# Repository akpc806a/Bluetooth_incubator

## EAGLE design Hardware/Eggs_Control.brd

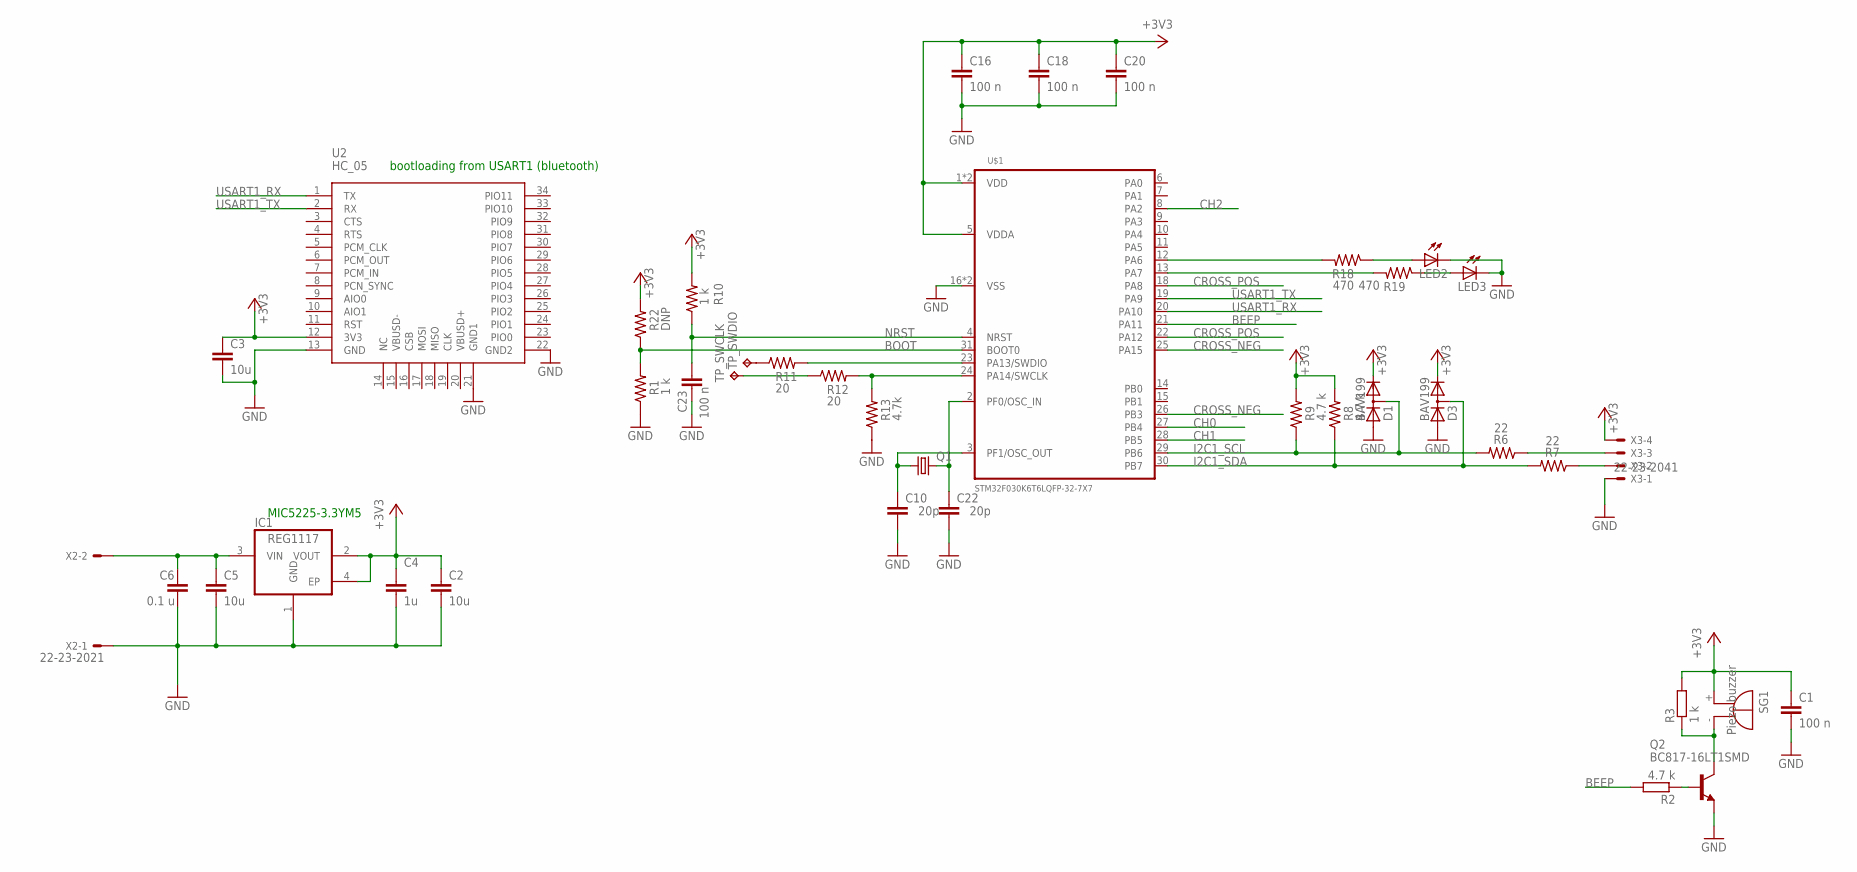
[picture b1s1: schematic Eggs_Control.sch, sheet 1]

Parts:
C1, C16, C18, C20, C23: 100 n; C0603
C2, C3, C5: 10u; C0805
C4: 1u; C0603
C6: 0.1 u; C0603
C10, C22: 20p; C0603
D1, D3: BAV199; SOT23
IC1: REG1117; SOT223
LED2, LED3: LED_ESML0603; LED_SML0603
Q1: CRYSTALSM49; SM49
Q2: BC817-16LT1SMD; SOT23-BEC
R1, R3, R10: 1 k; R0603
R2, R8, R9: 4.7 k; R0603
R6, R7: 22; R0603
R11, R12: 20; R0603
R13: 4.7k; R0603
R18, R19: 470; R0603
R22: DNP; R0603
SG1: Piezo buzzer; F/HMB
TP_SWCLK: TPTP10SQ; TP10SQ
TP_SWDIO: TPTP10SQ; TP10SQ
U2: HC_05; BLUETOOTH_SMD
U$1: STM32F030K6T6LQFP-32-7X7; LQFP32-7X7
X2: 22-23-2021
X3: 22-23-2041

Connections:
+3V3: C1.1, C2.1, C3.1, C4.1, C16.1, C18.1, C20.1, D1.2 (C), D3.2 (C), IC1.2 (VOUT), IC1.4 (EP), R3.2, R8.2, R9.2, R10.2, R22.2, SG1.+, U2.12 (3V3), U$1.1 (VDD), U$1.5 (VDDA), U$1.17 (VDD), X3.4; also elsewhere on the board
BEEP: R2.2, U$1.21 (PA11)
BOOT: R1.2, R22.1, U$1.31 (BOOT0)
CH0: U$1.27 (PB4); also elsewhere on the board
CH1: U$1.28 (PB5); also elsewhere on the board
CH2: U$1.8 (PA2); also elsewhere on the board
CROSS_NEG: U$1.25 (PA15), U$1.26 (PB3); also elsewhere on the board
CROSS_POS: U$1.18 (PA8), U$1.22 (PA12); also elsewhere on the board
GND: C1.2, C2.2, C3.2, C4.2, C5.2, C6.2, C10.2, C16.2, C18.2, C20.2, C22.2, C23.2, D1.1 (A), D3.1 (A), IC1.1 (GND), LED2.C, LED3.C, Q2.E, R1.1, R13.1, U2.13 (GND), U2.21 (GND1), U2.22 (GND2), U$1.16 (VSS), U$1.32 (VSS), X2.1, X3.1; also elsewhere on the board
I2C1_SCL: D1.3 (AC), R6.2, R9.1, U$1.29 (PB6)
I2C1_SDA: D3.3 (AC), R7.2, R8.1, U$1.30 (PB7)
unnamed: Q2.B, R2.1
unnamed: Q2.C, R3.1, SG1.-
unnamed: R18.2, U$1.12 (PA6)
unnamed: R19.2, U$1.13 (PA7)
unnamed: R7.1, X3.2
unnamed: R6.1, X3.3
unnamed: LED2.A, R18.1
unnamed: LED3.A, R19.1
unnamed: R11.2, U$1.23 (PA13/SWDIO)
unnamed: R12.2, R13.2, U$1.24 (PA14/SWCLK)
unnamed: R11.1, TP_SWDIO.TP
unnamed: R12.1, TP_SWCLK.TP
unnamed: C5.1, C6.1, IC1.3 (VIN), X2.2
unnamed: C22.1, Q1.2, U$1.2 (PF0/OSC_IN)
unnamed: C10.1, Q1.1, U$1.3 (PF1/OSC_OUT)
NRST: C23.1, R10.1, U$1.4 (NRST)
USART1_RX: U2.1 (TX), U$1.20 (PA10)
USART1_TX: U2.2 (RX), U$1.19 (PA9)

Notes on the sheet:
MIC5225-3.3YM5
bootloading from USART1 (bluetooth)

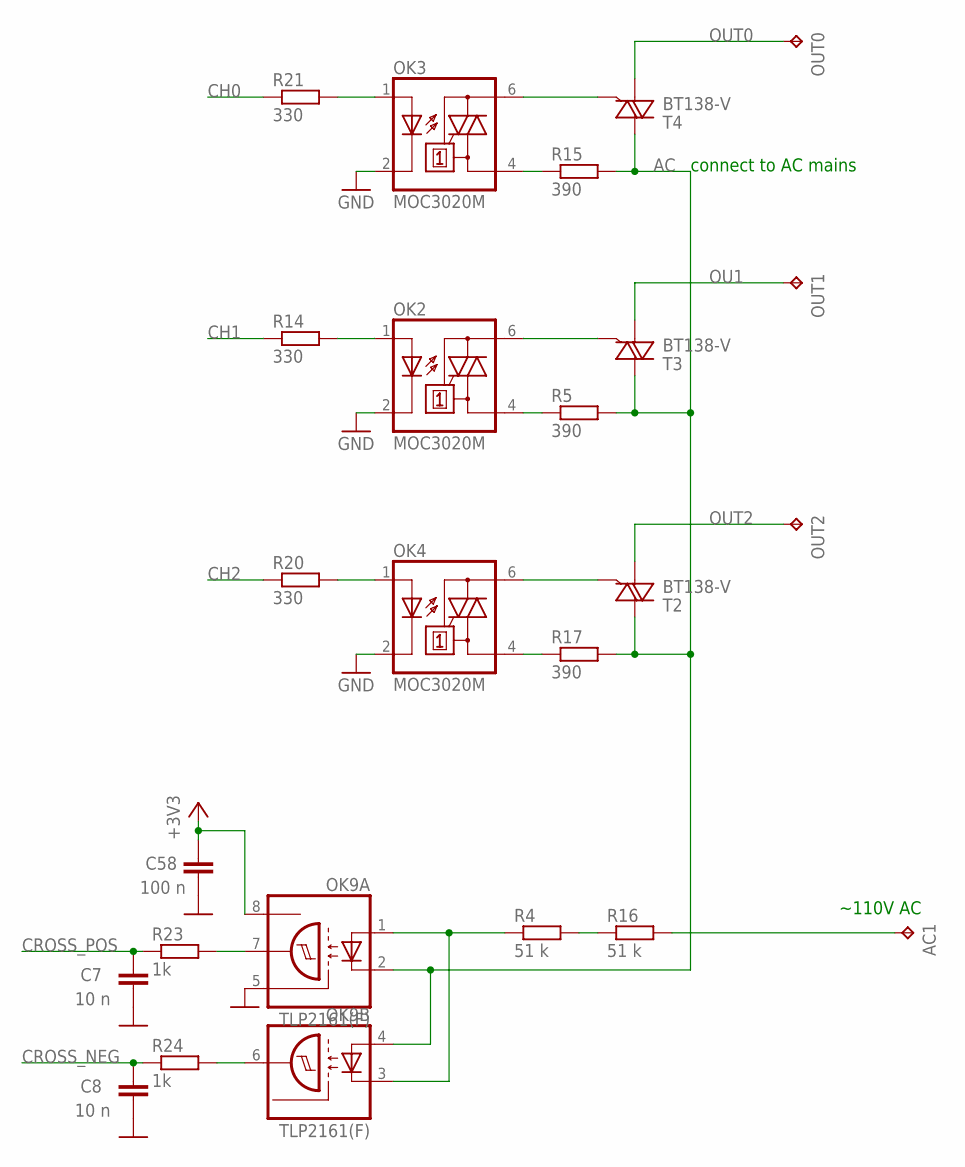
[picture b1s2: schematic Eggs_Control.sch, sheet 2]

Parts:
AC1: TPPAD1-17; P1-17
C7, C8: 10 n; C0603
C58: 100 n; C0603
OK2, OK3, OK4: MOC3020M; DIL06
OK9: TLP2161(F); SOIC08-FAIRCHILD
OUT0, OUT1, OUT2: TPPAD1-17; P1-17
R4, R16: 51 k; R1206
R5, R15, R17: 390; R0603
R14, R20, R21: 330; R0603
R23, R24: 1k; R0603
T2, T3, T4: BT138-V; TO220BV

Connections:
+3V3: C58.1, OK9.8 (VCC); also elsewhere on the board
AC: OK9.2 (C), OK9.4 (A), R5.2, R15.2, R17.2, T2.T2 (A2), T3.T2 (A2), T4.T2 (A2)
CH0: R21.1; also elsewhere on the board
CH1: R14.1; also elsewhere on the board
CH2: R20.1; also elsewhere on the board
CROSS_NEG: C8.1, R24.1; also elsewhere on the board
CROSS_POS: C7.1, R23.1; also elsewhere on the board
GND: C7.2, C8.2, C58.2, OK2.2 (C), OK3.2 (C), OK4.2 (C), OK9.5 (GND); also elsewhere on the board
unnamed: OK9.1 (A), OK9.3 (C), R4.1
unnamed: AC1.TP, R16.2
unnamed: OK9.7 (OUT), R23.2
unnamed: OK9.6 (OUT), R24.2
unnamed: OK2.1 (A), R14.2
unnamed: R4.2, R16.1
unnamed: OK4.1 (A), R20.2
unnamed: OK4.4 (A1), R17.1
unnamed: OK4.6 (A2), T2.G
unnamed: OK2.4 (A1), R5.1
unnamed: OK2.6 (A2), T3.G
unnamed: OK3.1 (A), R21.2
unnamed: OK3.4 (A1), R15.1
unnamed: OK3.6 (A2), T4.G
OU1: OUT1.TP, T3.T1 (A1)
OUT0: OUT0.TP, T4.T1 (A1)
OUT2: OUT2.TP, T2.T1 (A1)

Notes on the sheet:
~110V AC
connect to AC mains

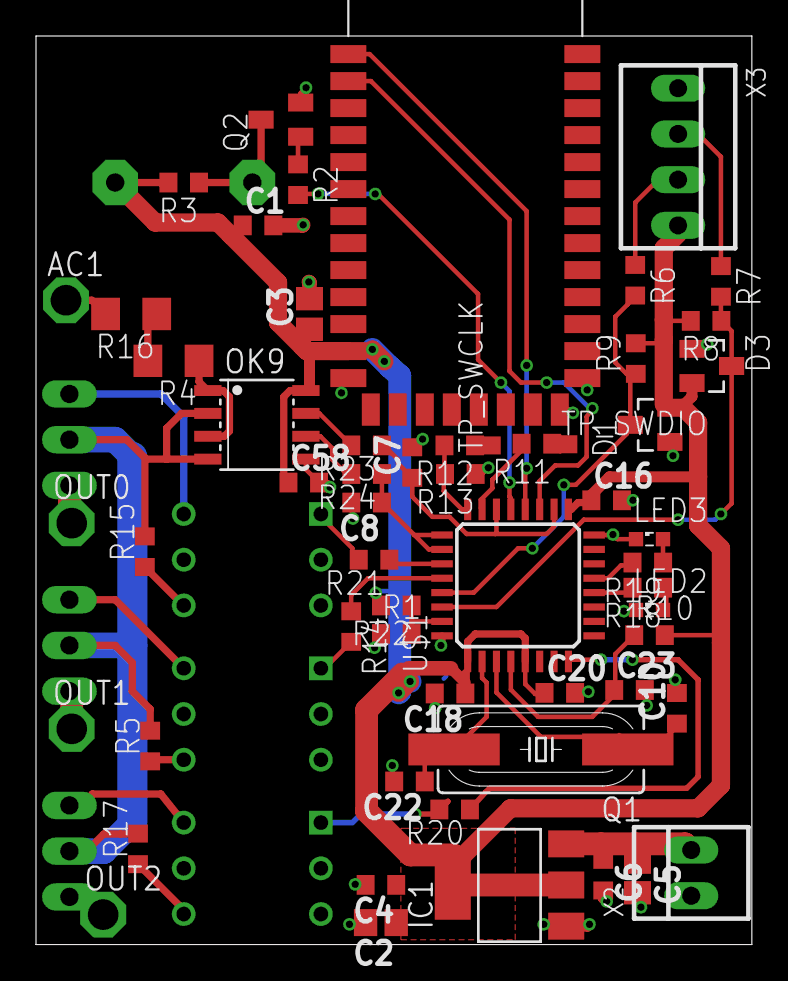
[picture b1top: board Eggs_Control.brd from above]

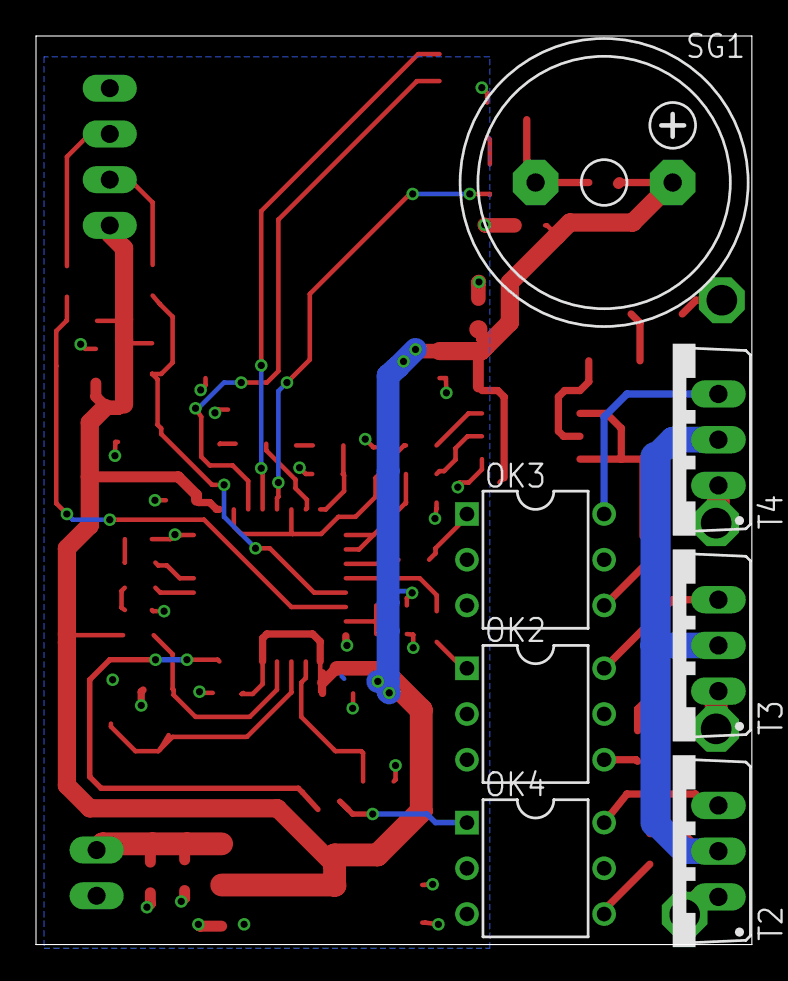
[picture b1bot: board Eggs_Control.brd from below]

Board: 2 copper layers, 39.8 x 50.5 mm, 64 parts (7 on the bottom side), 47 nets.

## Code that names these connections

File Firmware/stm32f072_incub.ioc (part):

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Mcu.Name=STM32F072R(8-B)Tx
Mcu.Package=LQFP64
Mcu.UserName=STM32F072RBTx
PA10.Mode=Asynchronous
PA10.Signal=USART1_RX
PA6.GPIOParameters=GPIO_Speed,GPIO_Label
PA6.GPIO_Label=LEDG
PA6.GPIO_Speed=GPIO_SPEED_HIGH
PA6.Signal=GPIO_Output
PA7.GPIOParameters=GPIO_Speed,GPIO_Label
PA7.GPIO_Label=LEDR
PA7.GPIO_Speed=GPIO_SPEED_HIGH
PA7.Signal=GPIO_Output
PA9.Mode=Asynchronous
PA9.Signal=USART1_TX
PB3.GPIOParameters=GPIO_Speed,GPIO_Label
PB3.GPIO_Label=CH1
PB3.GPIO_Speed=GPIO_SPEED_HIGH
PB3.Signal=GPIO_Output
PB6.Mode=I2C
PB6.Signal=I2C1_SCL
PB7.Mode=I2C
PB7.Signal=I2C1_SDA
PB9.GPIOParameters=GPIO_Speed,GPIO_Label
PB9.GPIO_Label=CH2
PB9.GPIO_Speed=GPIO_SPEED_HIGH
PB9.Signal=GPIO_Output
PC11.GPIOParameters=GPIO_Label
PC11.GPIO_Label=CROSS_POS
PC11.Signal=GPXTI11
PC12.GPIOParameters=GPIO_Label
PC12.GPIO_Label=CROSS_NEG
PC12.Signal=GPXTI12
PD2.GPIOParameters=GPIO_Speed,GPIO_Label
PD2.GPIO_Label=CH0
PD2.GPIO_Speed=GPIO_SPEED_HIGH
PD2.Signal=GPIO_Output
PF0-OSC_IN.Mode=HSE-External-Oscillator
PF0-OSC_IN.Signal=RCC_OSC_IN
PF1-OSC_OUT.Mode=HSE-External-Oscillator
PF1-OSC_OUT.Signal=RCC_OSC_OUT
RCC.SYSCLKFreq_VALUE=48000000
RCC.SYSCLKSource=RCC_SYSCLKSOURCE_PLLCLK
board=stm32f072_incub

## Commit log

2016-10-24 initial commit
    - hardware tested
    - firmware tested with PC computer software (including Modbus interface,
    temperature regulator, humidity control, timer)
2017-01-03 gitignore updated
2017-01-03 LEDs corrected
2017-01-03 LEDs fixed in project
2017-01-03 mobile application source code added
2017-01-03 protection implemented
2017-01-04 corrected modbus response bug
2017-01-23 hybrid temperature control algorithm implemented
    + minor fixes of mobile app
2017-01-26 automatic PI tuning -- initial version
2017-01-28 release of version 0.1 software
2017-01-29 minor fixes in firmware, manual (initial version) added
2017-01-29 hybrid mode fixed
2017-01-29 minor fixes in documentation
2017-01-29 added pdf circuit
2017-01-30 updated manual (after proofreading)
2017-02-03 text aligment in main.c fixed
